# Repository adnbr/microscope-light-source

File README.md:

Microscope Light Source
=======================

A simple PWM capable constant current source for a high brightness LED
based around an ATtiny13 and an LM317 voltage regulator. 

The board has been designed to be primarily one-sided, it should be
possible to etch it DIY. This hasn't been tested though. The top copper
layer only has a ground fill and the extra unused pins brought out to
pads for possible use at a later date. 

You can find out more [here](http://bit.ly/1d51tgB).

Mentioned [here](http://bit.ly/17b90Ci).

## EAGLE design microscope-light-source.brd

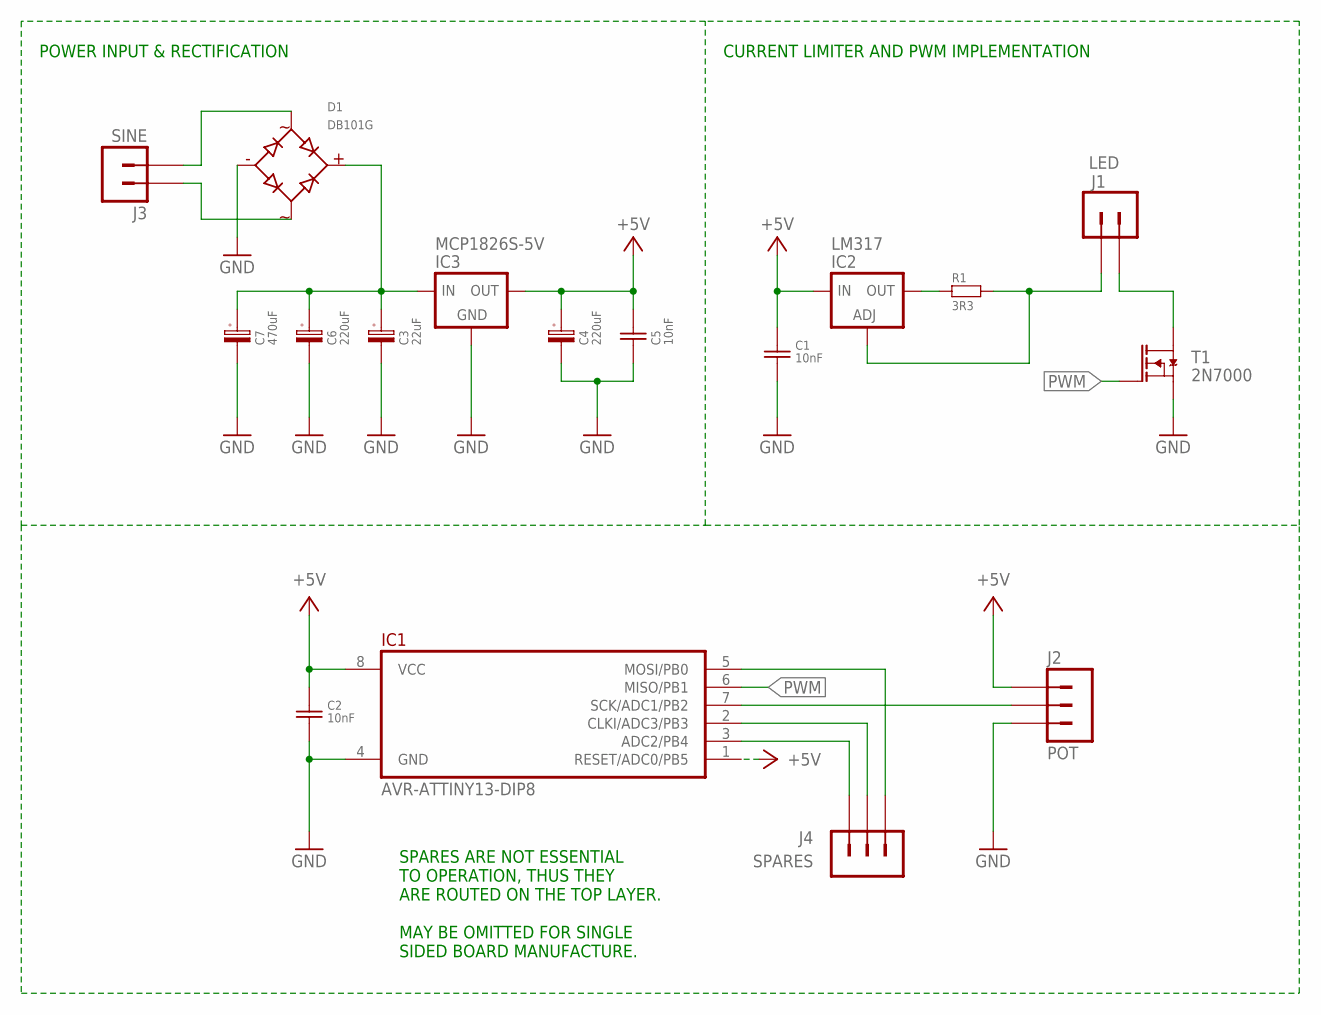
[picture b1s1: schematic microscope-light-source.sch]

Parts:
C1, C2, C5: 10nF; CAPACITOR-5MM-GRID
C3: 22uF; CAPACITOR-RADIAL-5MM
C4, C6: 220uF; CAPACITOR-RADIAL-5MM
C7: 470uF; CAPACITOR-RADIAL-10MM
D1: DB101G; DIL04-3-BRIDGE-RECTIFIER
IC1: AVR-ATTINY13-DIP8; DIL08-3
IC2: LM317; TO220-HORZ-DRILL
IC3: MCP1826S-5V; TO220-HORZ-DRILL
J1: LED; J02-LONG
J2: POT; J03-LONG
J3: SINE; J02-LONG
J4: SPARES; J03-NOSILK
R1: 3R3; RESISTOR-4MMX10MM/9
T1: 2N7000; TO92-TRIANGLE

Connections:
+5V: C1.1, C2.1, C4.A, C5.1, IC1.1 (RESET/ADC0/PB5), IC1.8 (VCC), IC2.3 (IN), IC3.3 (OUT), J2.1
GND: C1.2, C2.2, C3.C, C4.C, C5.2, C6.C, C7.C, D1.-, IC1.4 (GND), IC3.2 (GND), J2.3, T1.1 (SOURCE)
unnamed: IC2.2 (OUT), R1.2
unnamed: IC2.1 (ADJ), J1.1, R1.1
unnamed: J1.2, T1.3 (DRAIN)
unnamed: IC1.3 (ADC2/PB4), J4.3
unnamed: IC1.7 (SCK/ADC1/PB2), J2.2
unnamed: IC1.2 (CLKI/ADC3/PB3), J4.2
unnamed: C3.A, C6.A, C7.A, D1.+, IC3.1 (IN)
unnamed: D1.SINE0, J3.2
unnamed: D1.SINE1, J3.1
unnamed: IC1.5 (MOSI/PB0), J4.1
PWM: IC1.6 (MISO/PB1), T1.2 (GATE)

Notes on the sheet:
CURRENT LIMITER AND PWM IMPLEMENTATION
POWER INPUT & RECTIFICATION
SPARES ARE NOT ESSENTIAL TO OPERATION, THUS THEY ARE ROUTED ON THE TOP LAYER. MAY BE OMITTED FOR SINGLE SIDED BOARD MANUFACTURE.

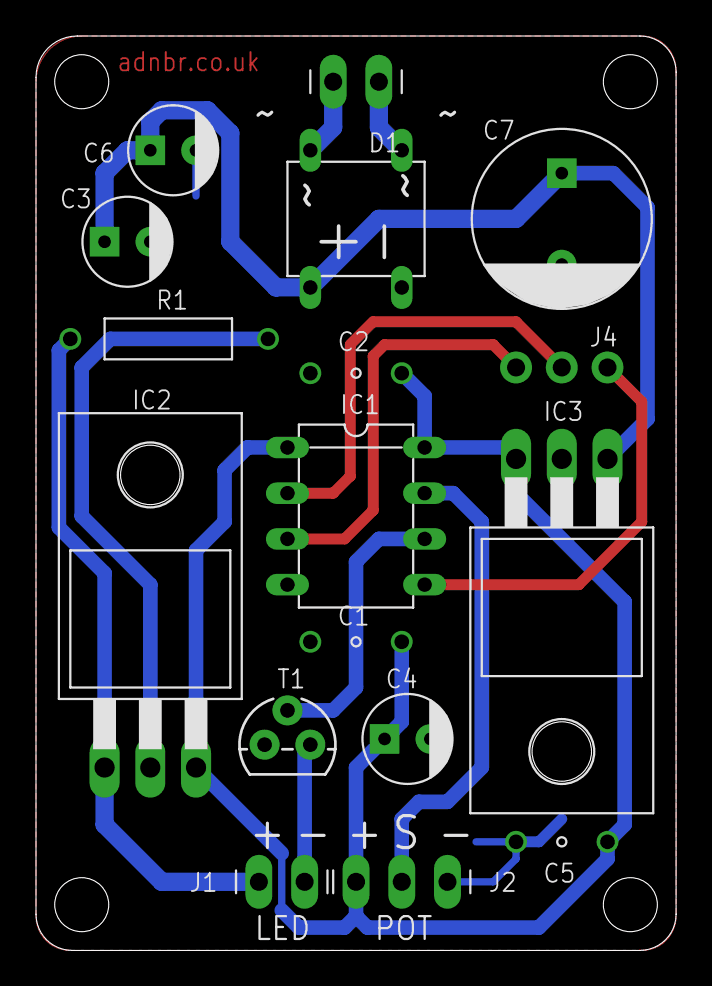
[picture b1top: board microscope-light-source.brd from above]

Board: 2 copper layers, 35.6 x 50.8 mm, 17 parts (0 on the bottom side), 13 nets.

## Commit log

2013-08-11 First commit.
2013-08-18 C values, board re-jig
    Values added for capacitors.
    Voltage regulator rotated 180 deg to simplify trace routing.
2013-08-18 Code first commit
    Inc. makefile.
    Not tested.
2013-08-19 Code & makefile
    Untested (Can't find the ISP programmer!)
2013-08-31 Readme & Code
    Moved to 10 bit ADC result. Smoother output. 1023 mapped to 255 using
    Arduino map function, see comments for link.
    All data filtered now, some stepping while changing values, not an
    issue. Now more stable in the lower ranges, won't jitter as easily when
    on the bounds of off segment.
    Now phase correct PWM.
2014-03-01 Rewritten, easier to read, use, etc.
    8-bit ADC directly to PWM. dedicated setup/read/write functions for ADC
    and PWM.
    Clearer comments for bit-wrangling sections of the setup (mentions
    appropriate tables in datasheet for future reference.)
2014-03-01 Tabs. Grrr.
2014-03-06 Catastrophic ADC error, re-map
    Fixed catastrophic problem with ADC - not an issue here, but poor form.
    Also re-introduced mapping (from Arduino library) so the full range of
    brightness is available past "off". ~712 bytes written to flash.
